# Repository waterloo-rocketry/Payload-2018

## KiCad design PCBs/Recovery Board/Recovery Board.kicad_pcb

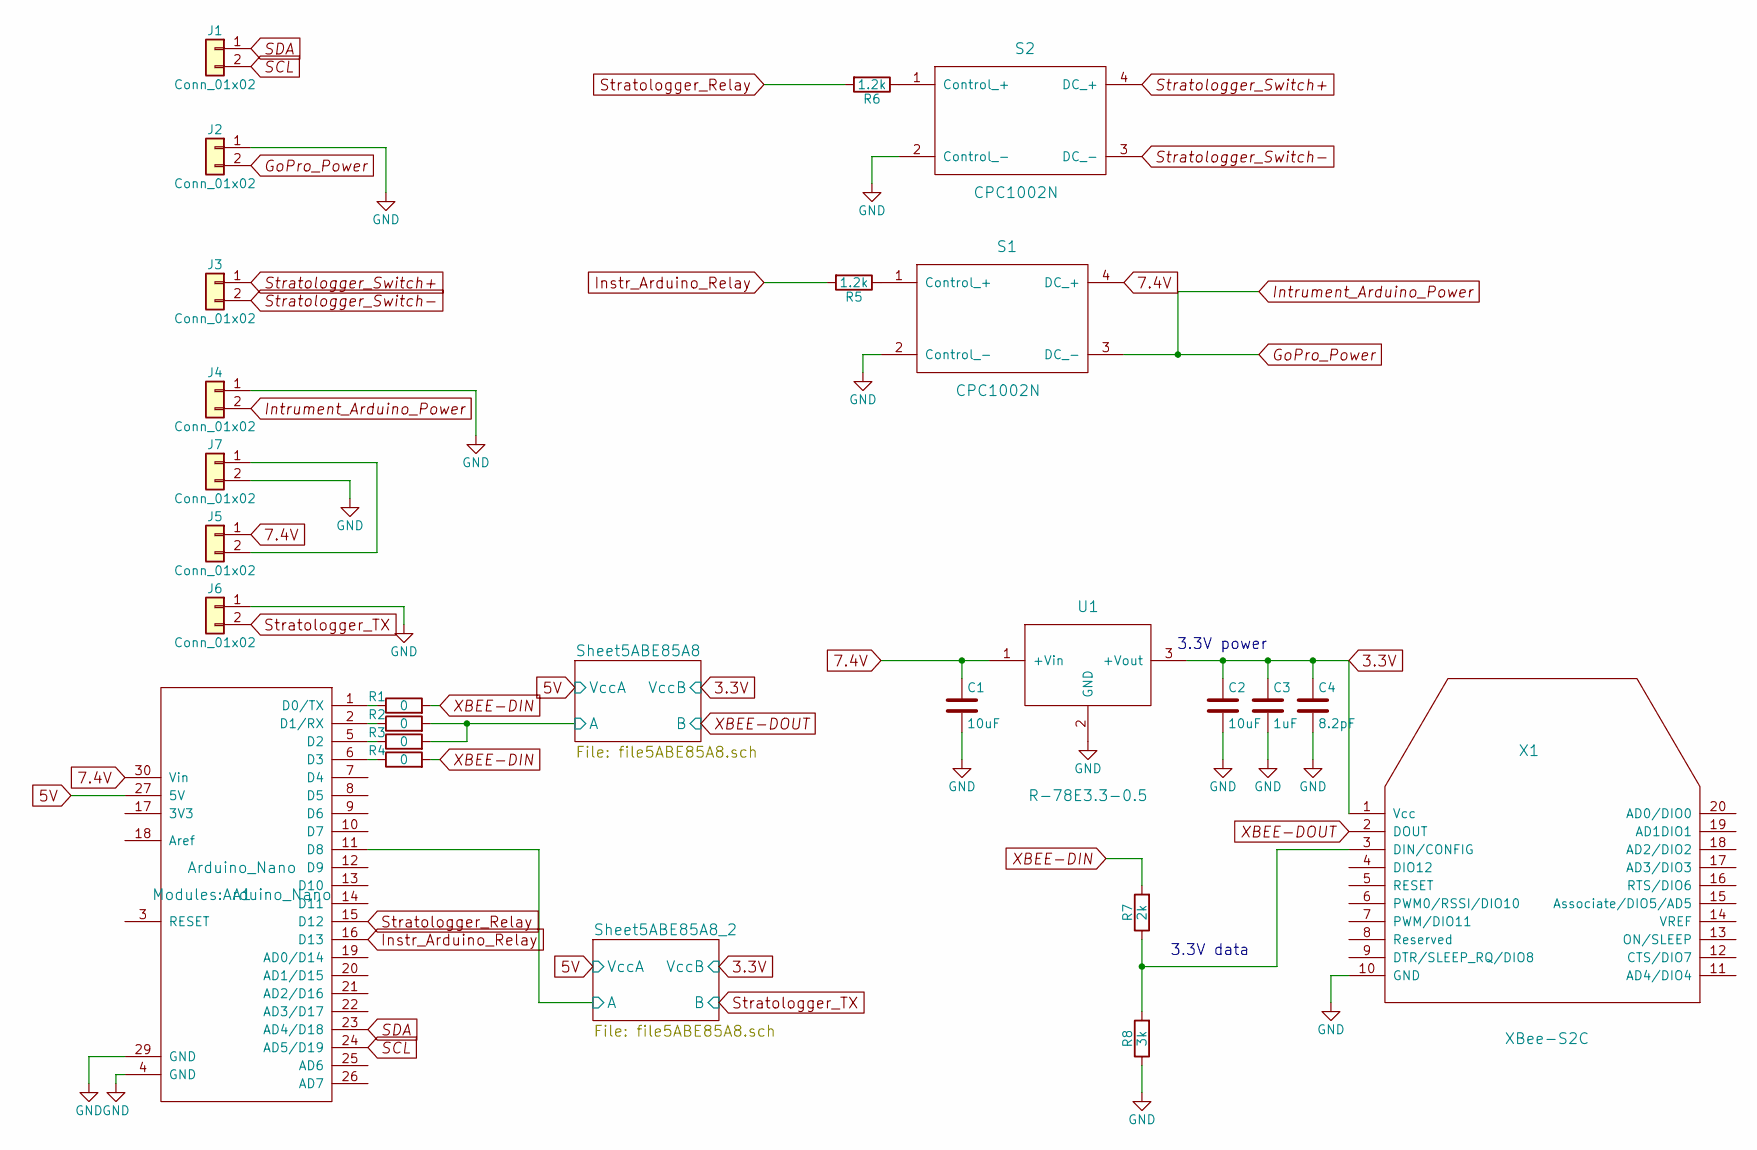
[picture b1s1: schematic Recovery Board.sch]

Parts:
A1: Arduino_Nano
C1, C2: 10uF; C_0805_HandSoldering
C3: 1uF; C_0805_HandSoldering
C4: 8.2pF; C_0805_HandSoldering
J1, J2, J3, J4, J6: Conn_01x02; molex_kk_22-23-2021
J5, J7: Conn_01x02; JST_PH_B2B-PH-K_02x2.00mm_Straight
R1, R2, R3, R4: 0; R_0805_HandSoldering
R5, R6: 1.2k; R_0805_HandSoldering
R7: 2k; R_0805_HandSoldering
R8: 3k; R_0805_HandSoldering
S1, S2: CPC1002N; CPC1002NTR
U1: R-78E3.3-0.5; SIP3
X1: XBee-S2C; XBEE-1

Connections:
3.3V: C2.1, C3.1, C4.1, U1.3 (+Vout), X1.1 (Vcc); also elsewhere on the board
5V: A1.27 (5V); also elsewhere on the board
7.4V: A1.30 (Vin), C1.1, J5.1, S1.4 (DC_+), U1.1 (+Vin)
/Sheet5ABE85A8/A: R2.2, R3.2; also elsewhere on the board
/Sheet5ABE85A8_2/A: A1.11 (D8); also elsewhere on the board
GND: A1.4 (GND), A1.29 (GND), C1.2, C2.2, C3.2, C4.2, J2.1, J4.1, J6.1, J7.2, R8.1, S1.2 (Control_-), S2.2 (Control_-), U1.2 (GND), X1.10 (GND); also elsewhere on the board
GoPro_Power: J2.2, J4.2, S1.3 (DC_-)
Instr_Arduino_Relay: A1.16 (D13), R5.2
unnamed: A1.1 (D0/TX), R1.1
unnamed: A1.2 (D1/RX), R2.1
unnamed: A1.5 (D2), R3.1
unnamed: A1.6 (D3), R4.1
unnamed: J5.2, J7.1
unnamed: R5.1, S1.1 (Control_+)
unnamed: R6.1, S2.1 (Control_+)
unnamed: R7.1, R8.2, X1.3 (DIN/CONFIG)
SCL: A1.24 (AD5/D19), J1.2
SDA: A1.23 (AD4/D18), J1.1
Stratologger_Relay: A1.15 (D12), R6.2
Stratologger_Switch+: J3.1, S2.4 (DC_+)
Stratologger_Switch-: J3.2, S2.3 (DC_-)
Stratologger_TX: J6.2; also elsewhere on the board
XBEE-DIN: R1.2, R4.2, R7.2
XBEE-DOUT: X1.2 (DOUT); also elsewhere on the board

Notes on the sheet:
3.3V data
3.3V power

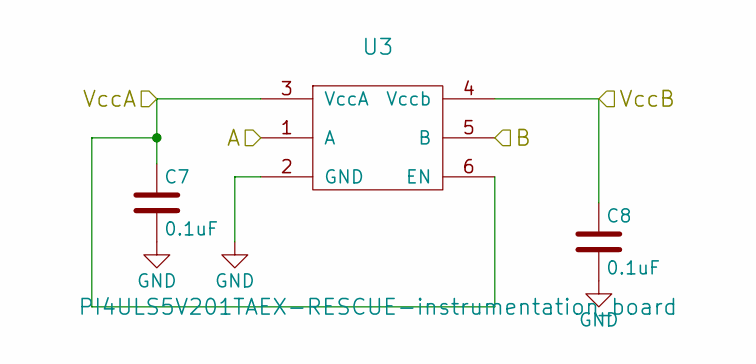
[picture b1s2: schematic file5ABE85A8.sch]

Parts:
C5, C6: 0.1uF; C_0805_HandSoldering
U2: PI4ULS5V201TAEX-RESCUE-instrumentation_board; SOT-23-6_Handsoldering

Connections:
3.3V: C6.1, U2.4 (Vccb); also elsewhere on the board
5V: C5.1, U2.3 (VccA), U2.6 (EN); also elsewhere on the board
/Sheet5ABE85A8/A: U2.1 (A); also elsewhere on the board
GND: C5.2, C6.2, U2.2 (GND); also elsewhere on the board
XBEE-DOUT: U2.5 (B); also elsewhere on the board

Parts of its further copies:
C7, C8: 0.1uF; C_0805_HandSoldering
U3: PI4ULS5V201TAEX-RESCUE-instrumentation_board; SOT-23-6_Handsoldering

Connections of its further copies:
3.3V: C8.1, U3.4 (Vccb); also elsewhere on the board
5V: C7.1, U3.3 (VccA), U3.6 (EN); also elsewhere on the board
/Sheet5ABE85A8_2/A: U3.1 (A); also elsewhere on the board
GND: C7.2, C8.2, U3.2 (GND); also elsewhere on the board
Stratologger_TX: U3.5 (B); also elsewhere on the board

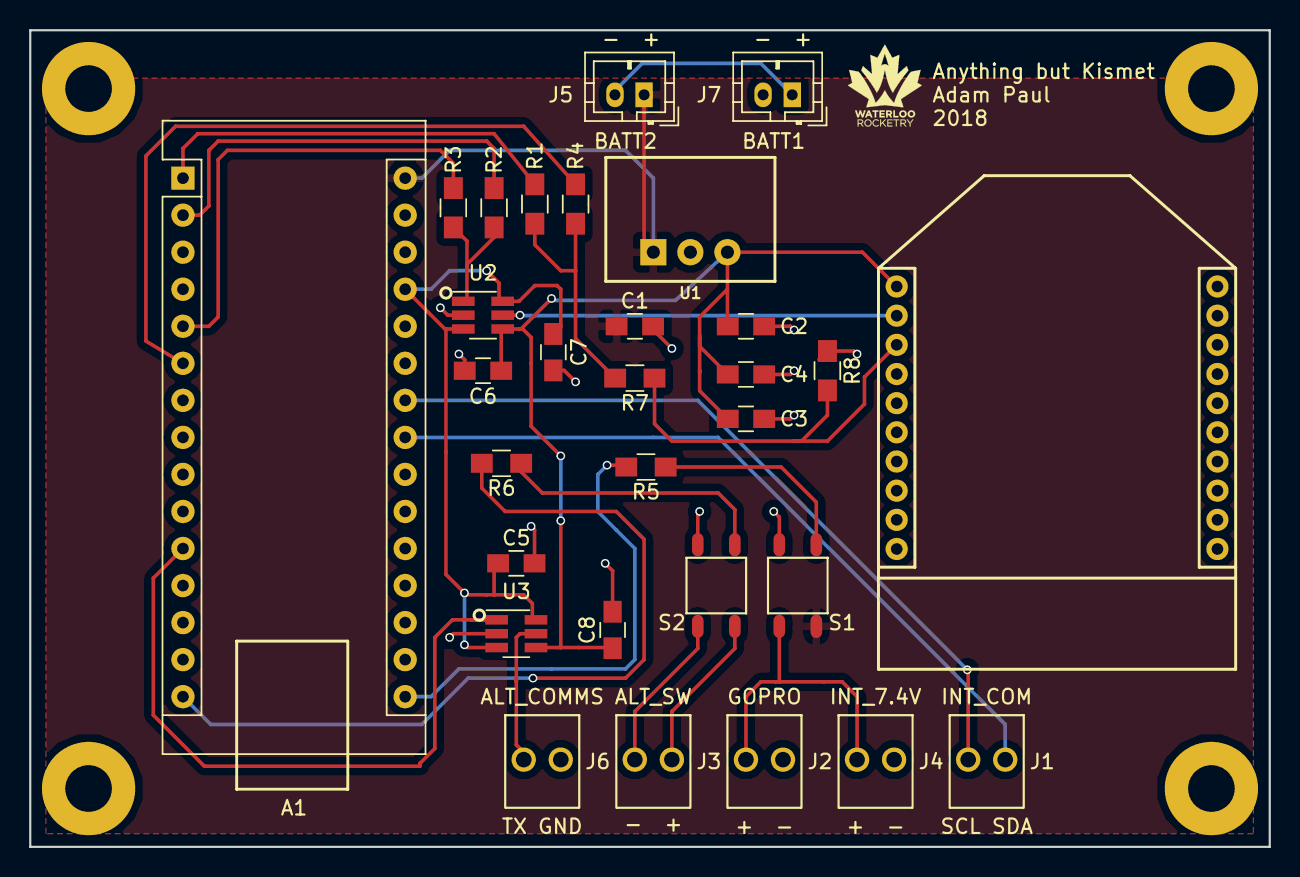
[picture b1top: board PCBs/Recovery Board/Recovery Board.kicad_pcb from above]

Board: 2 copper layers, 85.0 x 56.0 mm, 30 parts (0 on the bottom side), 24 nets.

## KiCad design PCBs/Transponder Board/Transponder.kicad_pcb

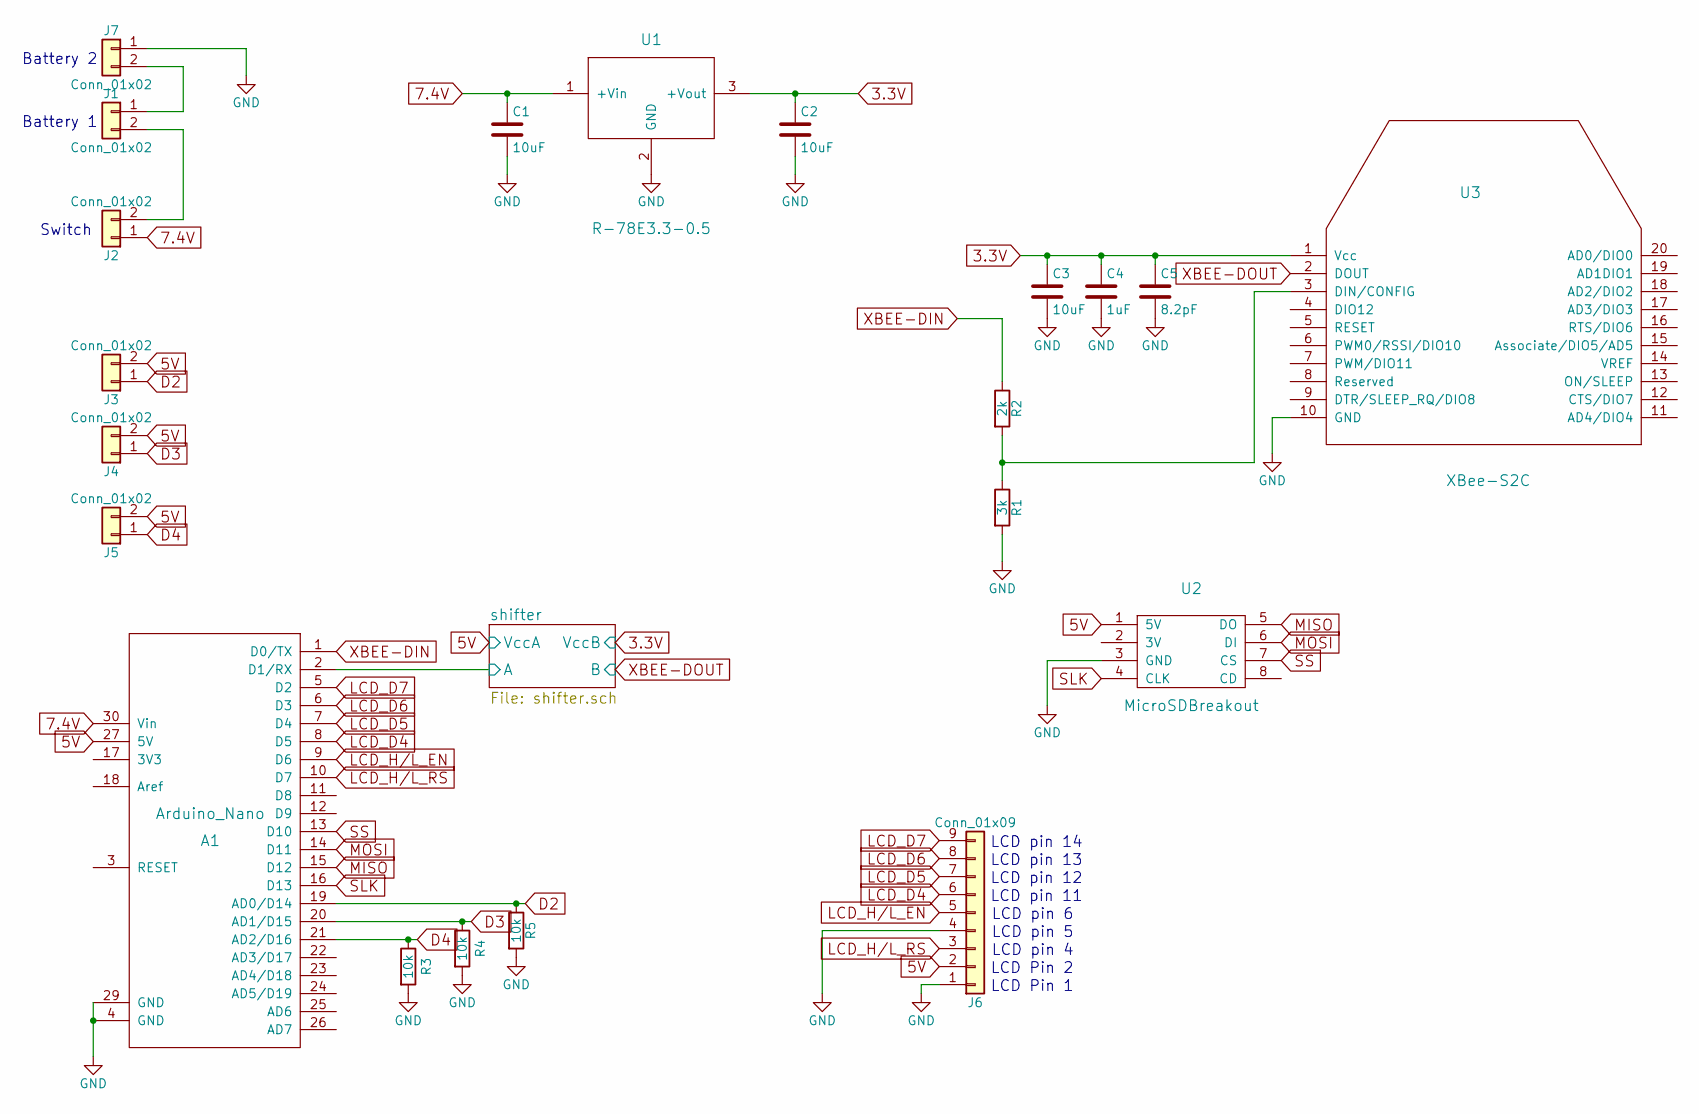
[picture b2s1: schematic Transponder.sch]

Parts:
A1: Arduino_Nano
C1, C2, C3: 10uF; C_0805_HandSoldering
C4: 1uF; C_0805_HandSoldering
C5: 8.2pF; C_0805_HandSoldering
J1, J7: Conn_01x02; JST_PH_B2B-PH-K_02x2.00mm_Straight
J2, J3, J4, J5: Conn_01x02; molex_kk_22-23-2021
J6: Conn_01x09; VI0921550000G
R1: 3k; R_0805_HandSoldering
R2: 2k; R_0805_HandSoldering
R3, R4, R5: 10k; R_0805_HandSoldering
U1: R-78E3.3-0.5; SIP3Large
U2: MicroSDBreakout; adafruit254
U3: XBee-S2C; XBEE-1

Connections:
3.3V: C2.1, C3.1, C4.1, C5.1, U1.3 (+Vout), U3.1 (Vcc); also elsewhere on the board
5V: A1.27 (5V), J3.2, J4.2, J5.2, J6.2, U2.1 (5V); also elsewhere on the board
7.4V: A1.30 (Vin), C1.1, J2.1, U1.1 (+Vin)
/shifter/A: A1.2 (D1/RX); also elsewhere on the board
D2: A1.19 (AD0/D14), J3.1, R5.1
D3: A1.20 (AD1/D15), J4.1, R4.1
D4: A1.21 (AD2/D16), J5.1, R3.1
GND: A1.4 (GND), A1.29 (GND), C1.2, C2.2, C3.2, C4.2, C5.2, J6.1, J6.4, J7.1, R1.2, R3.2, R4.2, R5.2, U1.2 (GND), U2.3 (GND), U3.10 (GND); also elsewhere on the board
LCD_D4: A1.8 (D5), J6.6
LCD_D5: A1.7 (D4), J6.7
LCD_D6: A1.6 (D3), J6.8
LCD_D7: A1.5 (D2), J6.9
LCD_H/L_EN: A1.9 (D6), J6.5
LCD_H/L_RS: A1.10 (D7), J6.3
MISO: A1.15 (D12), U2.5 (DO)
MOSI: A1.14 (D11), U2.6 (DI)
unnamed: J1.1, J7.2
unnamed: J1.2, J2.2
unnamed: R1.1, R2.2, U3.3 (DIN/CONFIG)
SLK: A1.16 (D13), U2.4 (CLK)
SS: A1.13 (D10), U2.7 (CS)
XBEE-DIN: A1.1 (D0/TX), R2.1
XBEE-DOUT: U3.2 (DOUT); also elsewhere on the board

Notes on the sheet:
LCD Pin 1
LCD Pin 2
LCD pin 4
LCD pin 5
LCD pin 6
LCD pin 11
LCD pin 12
LCD pin 13
LCD pin 14
Battery 1
Switch
Battery 2

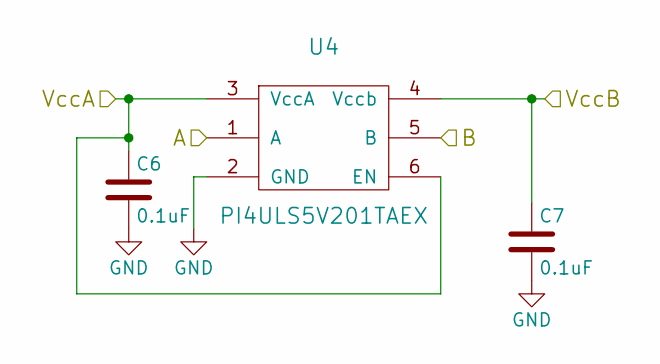
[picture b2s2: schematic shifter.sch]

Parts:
C6, C7: 0.1uF; C_0805_HandSoldering
U4: PI4ULS5V201TAEX; SOT-23-6_Handsoldering

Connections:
3.3V: C7.1, U4.4 (Vccb); also elsewhere on the board
5V: C6.1, U4.3 (VccA), U4.6 (EN); also elsewhere on the board
/shifter/A: U4.1 (A); also elsewhere on the board
GND: C6.2, C7.2, U4.2 (GND); also elsewhere on the board
XBEE-DOUT: U4.5 (B); also elsewhere on the board

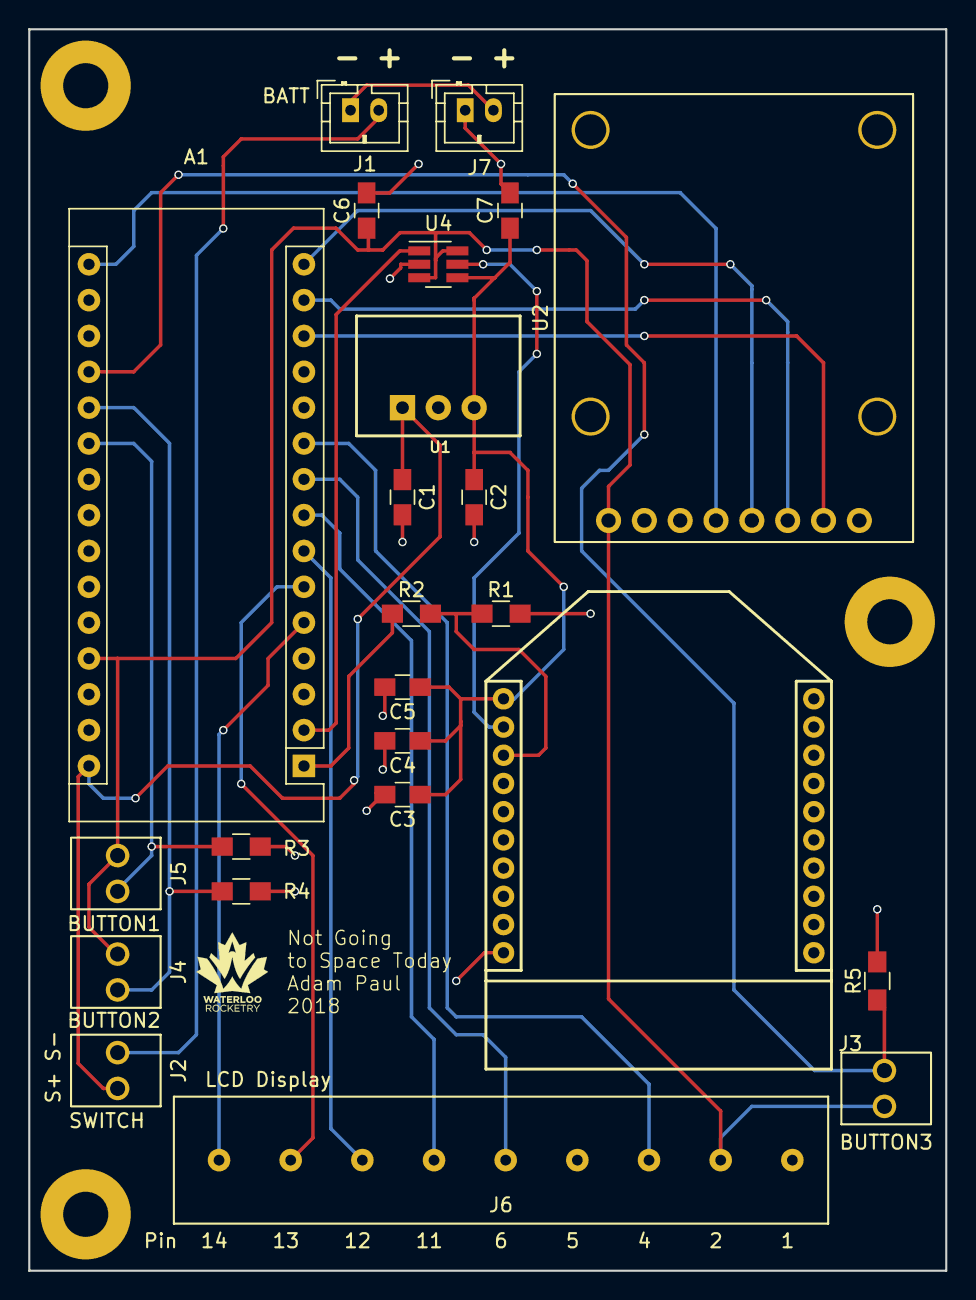
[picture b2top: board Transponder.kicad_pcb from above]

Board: 2 copper layers, 65.0 x 88.0 mm, 24 parts (0 on the bottom side), 23 nets.

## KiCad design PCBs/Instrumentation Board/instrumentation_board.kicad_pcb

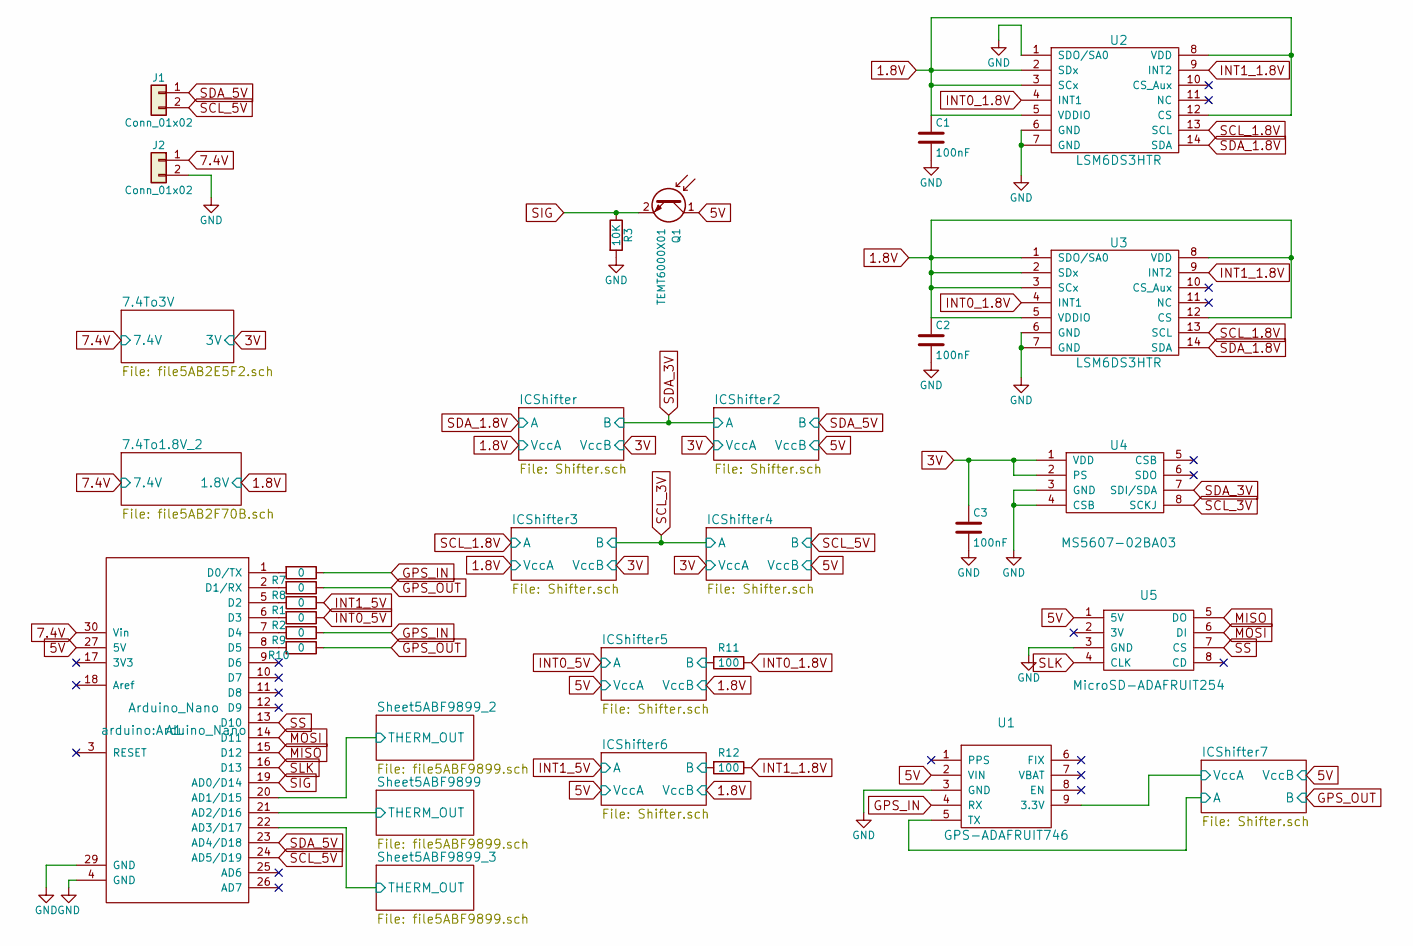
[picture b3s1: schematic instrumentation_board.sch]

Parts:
A1: Arduino_Nano
C1, C2, C3: 100nF; C_0805_HandSoldering
J1, J2: Conn_01x02; molex_kk_22-23-2021
Q1: TEMT6000X01
R1, R2, R7, R8, R9, R10: 0; R_0805_HandSoldering
R3: 10K; R_0805_HandSoldering
R11, R12: 100; R_0805_HandSoldering
U1: GPS-ADAFRUIT746; gps746
U2, U3: LSM6DS3HTR; LGA-14
U4: MS5607-02BA03; 8-SMD
U5: MicroSD-ADAFRUIT254; adafruit254

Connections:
1.8V: C1.1, C2.1, U2.2 (SDx), U2.3 (SCx), U2.5 (VDDIO), U2.8 (VDD), U2.12 (CS), U3.1 (SDO/SA0), U3.2 (SDx), U3.3 (SCx), U3.5 (VDDIO), U3.8 (VDD), U3.12 (CS); also elsewhere on the board
3V: C3.1, U4.1 (VDD), U4.2 (PS); also elsewhere on the board
5V: A1.27 (5V), Q1.1 (C), U1.2 (VIN), U5.1 (5V); also elsewhere on the board
7.4V: A1.30 (Vin), J2.1; also elsewhere on the board
/ICShifter7/A: U1.5 (TX); also elsewhere on the board
/ICShifter7/VccA: U1.9 (3.3V); also elsewhere on the board
/Sheet5ABF9899/THERM_OUT: A1.21 (AD2/D16); also elsewhere on the board
/Sheet5ABF9899_2/THERM_OUT: A1.20 (AD1/D15); also elsewhere on the board
/Sheet5ABF9899_3/THERM_OUT: A1.22 (AD3/D17); also elsewhere on the board
GND: A1.4 (GND), A1.29 (GND), C1.2, C2.2, C3.2, J2.2, R3.2, U1.3 (GND), U2.1 (SDO/SA0), U2.6 (GND), U2.7 (GND), U3.6 (GND), U3.7 (GND), U4.3 (GND), U4.4 (CSB), U5.3 (GND); also elsewhere on the board
GPS_IN: R7.1, R9.1, U1.4 (RX)
GPS_OUT: R8.1, R10.1; also elsewhere on the board
INT0_5V: R2.1; also elsewhere on the board
INT1_5V: R1.1; also elsewhere on the board
MISO: A1.15 (D12), U5.5 (DO)
MOSI: A1.14 (D11), U5.6 (DI)
unnamed: A1.1 (D0/TX), R7.2
unnamed: A1.2 (D1/RX), R8.2
unnamed: A1.5 (D2), R1.2
unnamed: A1.6 (D3), R2.2
unnamed: A1.7 (D4), R9.2
unnamed: A1.8 (D5), R10.2
SCL_1.8V: U2.13 (SCL), U3.13 (SCL); also elsewhere on the board
SCL_3V: U4.8 (SCKJ); also elsewhere on the board
SCL_5V: A1.24 (AD5/D19), J1.2; also elsewhere on the board
SDA_1.8V: U2.14 (SDA), U3.14 (SDA); also elsewhere on the board
SDA_3V: U4.7 (SDI/SDA); also elsewhere on the board
SDA_5V: A1.23 (AD4/D18), J1.1; also elsewhere on the board
SIG: A1.19 (AD0/D14), Q1.2 (E), R3.1
SLK: A1.16 (D13), U5.4 (CLK)
SS: A1.13 (D10), U5.7 (CS)

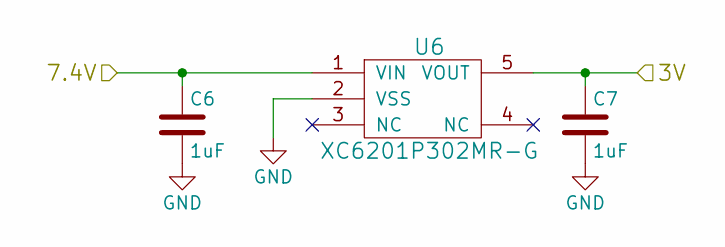
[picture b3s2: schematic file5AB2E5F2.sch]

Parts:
C6, C7: 1uF
U6: XC6201P302MR-G; SOT-23-5

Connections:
3V: C7.1, U6.5 (VOUT); also elsewhere on the board
7.4V: C6.1, U6.1 (VIN); also elsewhere on the board
GND: C6.2, C7.2, U6.2 (VSS); also elsewhere on the board

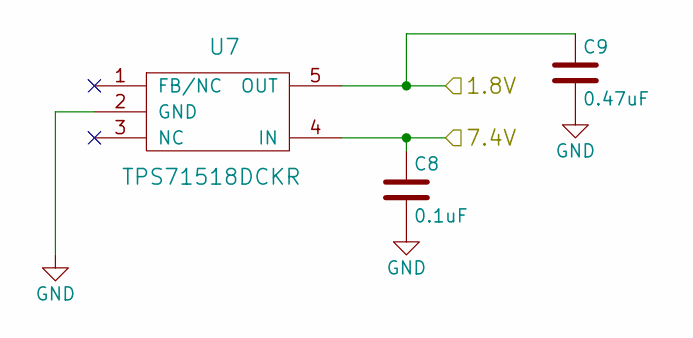
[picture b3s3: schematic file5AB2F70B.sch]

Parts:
C8: 0.1uF; C_0805_HandSoldering
C9: 0.47uF; C_0805_HandSoldering
U7: TPS71518DCKR; SOT-23-5

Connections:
1.8V: C9.1, U7.5 (OUT); also elsewhere on the board
7.4V: C8.1, U7.4 (IN); also elsewhere on the board
GND: C8.2, C9.2, U7.2 (GND); also elsewhere on the board

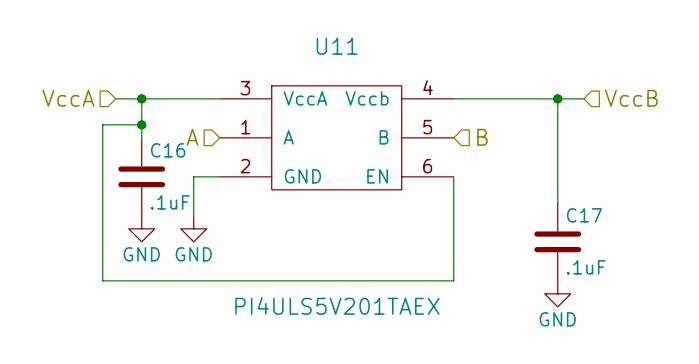
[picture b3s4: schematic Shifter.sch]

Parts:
C10, C11: .1uF; C_0805_HandSoldering
U8: PI4ULS5V201TAEX; SOT-23-6_Handsoldering

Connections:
3V: C10.1, U8.3 (VccA), U8.6 (EN); also elsewhere on the board
5V: C11.1, U8.4 (Vccb); also elsewhere on the board
GND: C10.2, C11.2, U8.2 (GND); also elsewhere on the board
SCL_3V: U8.1 (A); also elsewhere on the board
SCL_5V: U8.5 (B); also elsewhere on the board

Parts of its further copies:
C12, C13, C14, C15, C16, C17, C18, C19, C20, C21, C22, C23: .1uF; C_0805_HandSoldering
U9, U10, U11, U12, U13, U14: PI4ULS5V201TAEX; SOT-23-6_Handsoldering

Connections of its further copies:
1.8V: C12.1, C16.1, C21.1, C23.1, U9.3 (VccA), U9.6 (EN), U11.3 (VccA), U11.6 (EN), U13.4 (Vccb), U14.4 (Vccb); also elsewhere on the board
3V: C13.1, C14.1, C17.1, U9.4 (Vccb), U10.3 (VccA), U10.6 (EN), U11.4 (Vccb); also elsewhere on the board
5V: C15.1, C19.1, C20.1, C22.1, U10.4 (Vccb), U12.4 (Vccb), U13.3 (VccA), U13.6 (EN), U14.3 (VccA), U14.6 (EN); also elsewhere on the board
/ICShifter7/A: U12.1 (A); also elsewhere on the board
/ICShifter7/VccA: C18.1, U12.3 (VccA), U12.6 (EN); also elsewhere on the board
GND: C12.2, C13.2, C14.2, C15.2, C16.2, C17.2, C18.2, C19.2, C20.2, C21.2, C22.2, C23.2, U9.2 (GND), U10.2 (GND), U11.2 (GND), U12.2 (GND), U13.2 (GND), U14.2 (GND); also elsewhere on the board
GPS_OUT: U12.5 (B); also elsewhere on the board
INT0_5V: U13.1 (A); also elsewhere on the board
INT1_5V: U14.1 (A); also elsewhere on the board
SCL_1.8V: U9.1 (A); also elsewhere on the board
SCL_3V: U9.5 (B); also elsewhere on the board
SDA_1.8V: U11.1 (A); also elsewhere on the board
SDA_3V: U10.1 (A), U11.5 (B); also elsewhere on the board
SDA_5V: U10.5 (B); also elsewhere on the board

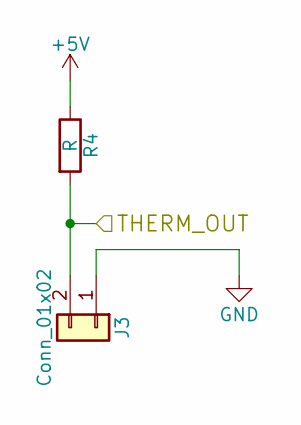
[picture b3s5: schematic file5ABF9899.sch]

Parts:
J3: Conn_01x02; molex_kk_22-23-2021
R4: R

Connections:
5V: R4.1; also elsewhere on the board
/Sheet5ABF9899_2/THERM_OUT: J3.2, R4.2; also elsewhere on the board
GND: J3.1; also elsewhere on the board

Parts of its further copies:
J4, J5: Conn_01x02; molex_kk_22-23-2021
R5, R6: R

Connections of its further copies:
5V: R5.1, R6.1; also elsewhere on the board
/Sheet5ABF9899/THERM_OUT: J4.2, R5.2; also elsewhere on the board
/Sheet5ABF9899_3/THERM_OUT: J5.2, R6.2; also elsewhere on the board
GND: J4.1, J5.1; also elsewhere on the board

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
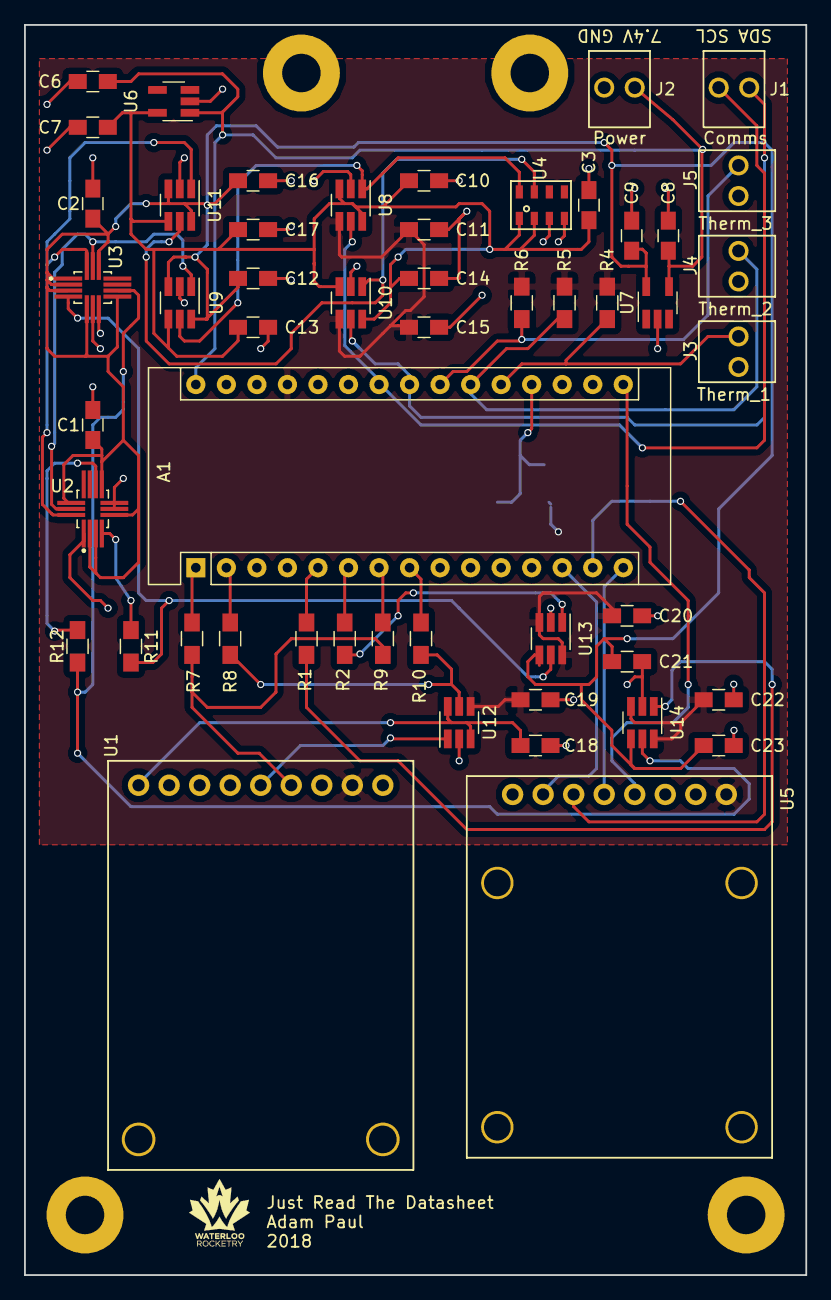
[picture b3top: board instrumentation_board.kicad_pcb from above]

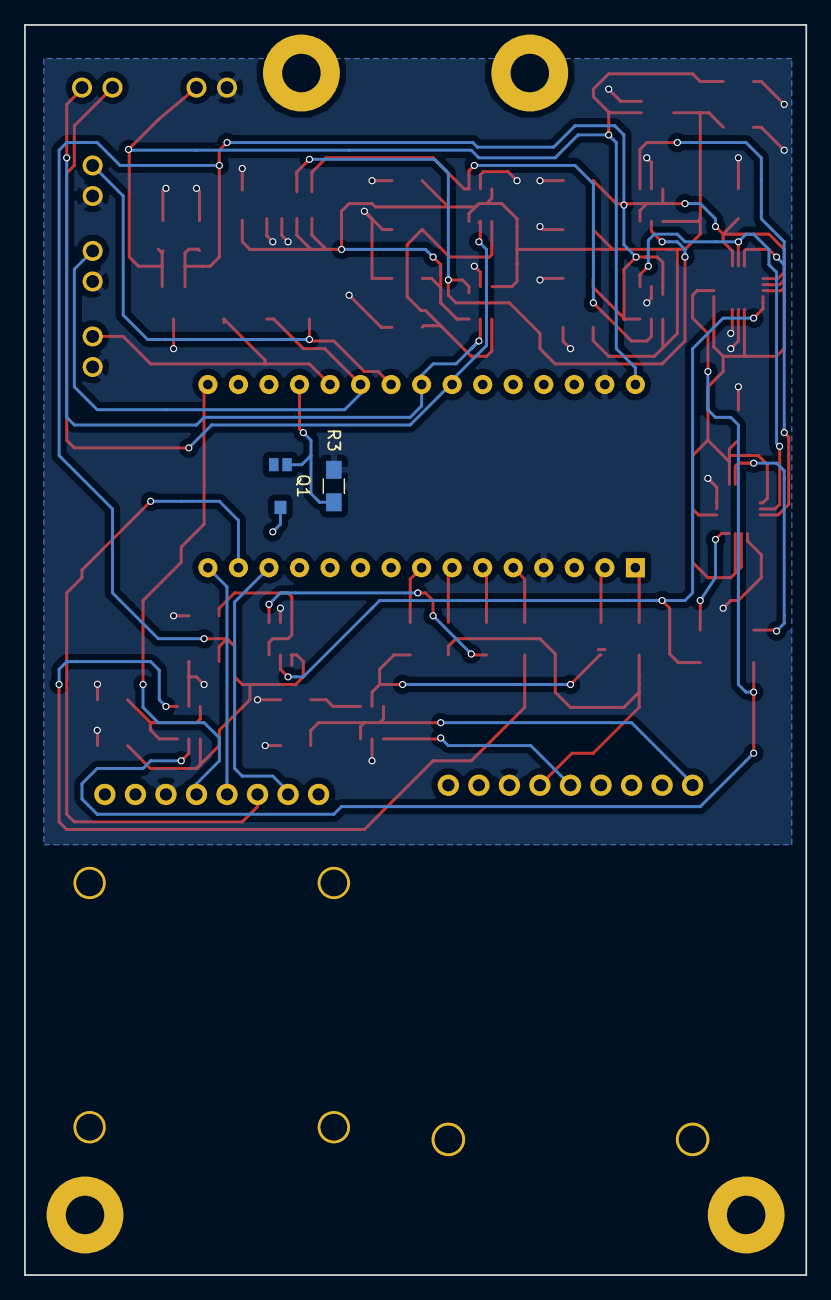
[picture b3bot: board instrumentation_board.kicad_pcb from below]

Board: 2 copper layers, 65.0 x 104.0 mm, 54 parts (2 on the bottom side), 35 nets.

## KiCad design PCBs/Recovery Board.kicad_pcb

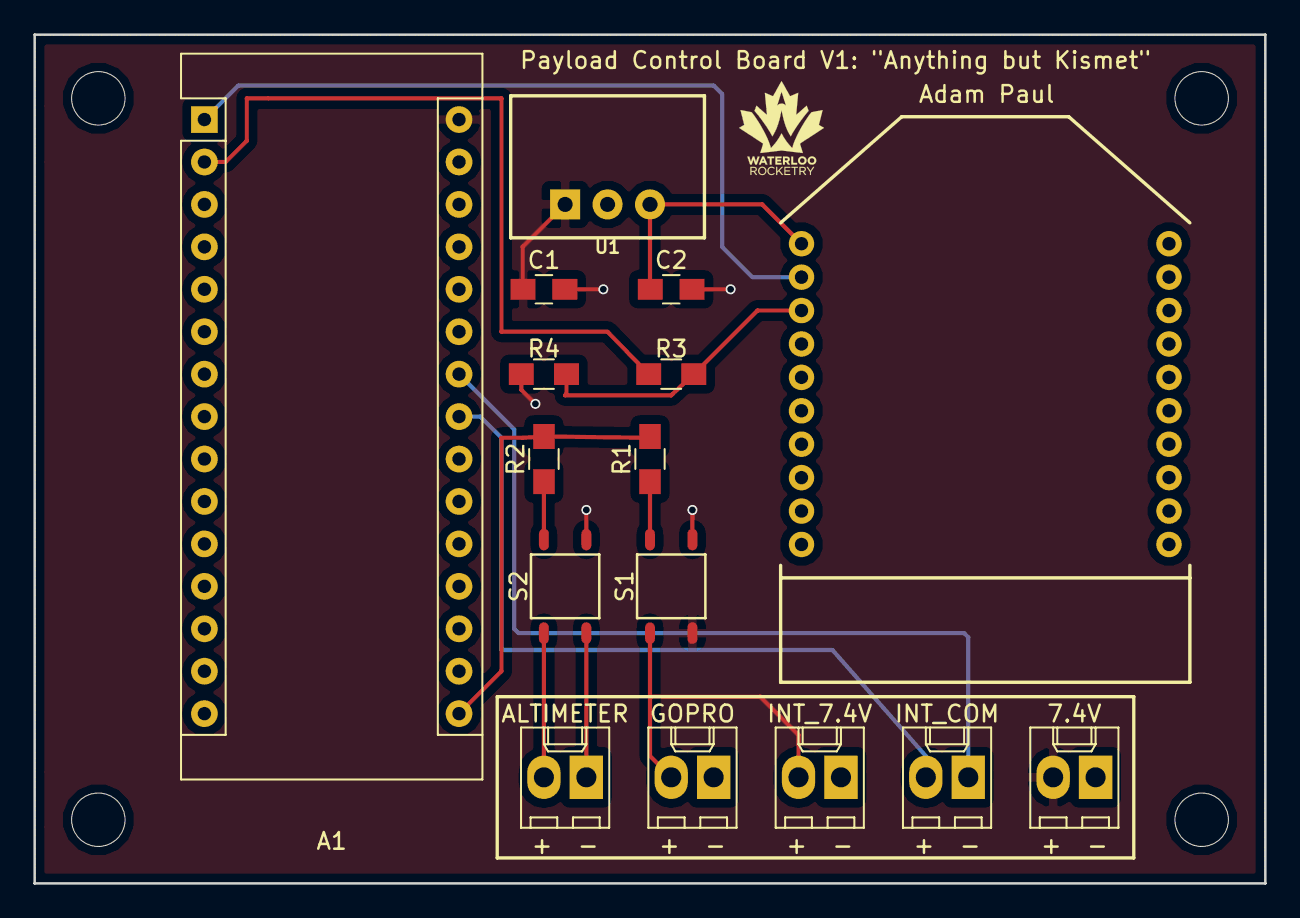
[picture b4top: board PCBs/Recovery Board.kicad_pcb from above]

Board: 2 copper layers, 73.7 x 50.8 mm, 16 parts (0 on the bottom side), 14 nets.

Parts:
7.4V: Conn_01x02; Molex_KK-6410-02_02x2.54mm_Straight
A1: Arduino_Nano
ALTIMETER: Conn_01x02; Molex_KK-6410-02_02x2.54mm_Straight
C1, C2: 10uF; C_0805_HandSoldering
GOPRO: Conn_01x02; Molex_KK-6410-02_02x2.54mm_Straight
INT_7.4V: Conn_01x02; Molex_KK-6410-02_02x2.54mm_Straight
INT_COM: Conn_01x02; Molex_KK-6410-02_02x2.54mm_Straight
R1, R2: 1.9k; R_0805_HandSoldering
R3: R3; R_0805_HandSoldering
R4: R4; R_0805_HandSoldering
S1, S2: CPC1002N; CPC1002NTR
U1: R-78E3.3-0.5; SIP3
X1: XBee-S2C; XBEE-1

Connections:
7.4V: 7.4V.2, A1.30, C1.1, S1.4, U1.1
GND: 7.4V.1, A1.4, A1.29, C1.2, C2.2, GOPRO.1, INT_7.4V.1, R4.1, S1.2, S2.2, U1.2, X1.10
GoPro_Power: GOPRO.2, INT_7.4V.2, S1.3
INSTRUMENT_ARDUINO_COMMS1: A1.23, INT_COM.2
INSTRUMENT_ARDUINO_COMMS2: A1.24, INT_COM.1
unnamed: R3.1, R4.2, X1.3
unnamed: A1.16, R1.2, R2.2
unnamed: C2.1, U1.3, X1.1
unnamed: R1.1, S1.1
unnamed: R2.1, S2.1
Stratologger_Switch+: ALTIMETER.2, S2.3
Stratologger_Switch-: ALTIMETER.1, S2.4
XBEE-DIN: A1.2, R3.2
XBEE-DOUT: A1.1, X1.2

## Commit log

2018-03-06 Fixed grounds and missing terminal
2018-03-08 Instrumentation board
2018-03-13 Instrumentation board for review
2018-03-14 Changes requested by alex
2018-03-21 added some new parts and i2c bus changes
2018-03-24 replace bidirectional shifters with ICs
2018-03-24 fixed swapped pins
2018-03-25 transponder board
2018-03-26 changes as per Alex's review
2018-03-27 pinout changes
2018-03-28 stashing changes
2018-03-28 Re-annotated
2018-03-28 Netlist Genorated
    Fixed multiple sheets with same name issue, generated netlist
2018-03-28 Started instrumentation Netlist
    Finished footprints for shifter, regulators and IMUs
2018-03-29 Continuing netlist
    Added barometric pressure sensor, started pattern for SD breakout board
2018-03-30 added various review changes
2018-03-30 swapped TX and RX pins
2018-03-30 weird merge
2018-03-30 Footprints updated
2018-03-31 Fixed weird merge issue (2)
2018-03-31 Added BOM and software outline
2018-03-31 testing slack integration
2018-04-01 review changes + instr board PCB
2018-04-01 finished traces on instr board
2018-04-01 edge cuts and screw holes
2018-04-03 Updated Recovery Netlist, started board updated layout
2018-04-03 completed layout for transponder board
2018-04-04 Continued new recovery board layout
2018-04-04 rerouted payload instr board and completed all changes per Alexs review
2018-04-04 transponder changes as per Alexs review
2018-04-04 fixed some outstanding instr issues, removed lots of vias
2018-04-04 Finished updating recovery board layout
    board layout, schematic and netlist up to date
2018-04-05 fixed outstanding changes on instr and transponder board
2018-04-06 swapped all mounting holes with plated ones, fixed disconnected components on recovery, added the 4 decoupling caps to recovery, fixed silk screen on pads in instr, fixed traces connecting through pa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
2018-04-07 Changed connectors for recovery board batteries
    Added a second connector for the other battery
    Moved connectors to top of board
    Replaced footprint with JST-PH
    Extended board width
2018-04-08 Changes to instr connectors
    Extended instr board length
    moved power connector to top of board
    removed I2C connector to top of board
2018-04-08 Fixed instr and recovery components per Alexs review
    Added IMU current limiting resistors
    Moved the caps near J4 on instr
    Swapped out phototransistor footprint
    Flipped I2C silk screen on J1 recovery
    Flipped GND and TX silk screen on J6 recovery
    renamed strat to alt on recovery silk screen
2018-04-09 Current limiting resistors
    Fixed structure of current limiting resistors on instr arduino
2018-04-09 Added Gerber Files
2018-04-10 Re-exported gerber
2018-04-10 Connector Changes
    Flipped the transponder jst-ph connectors
    Replaced the molex footprint on recovery with the correct one
2018-04-11 Re-Exported Gerber files with .05mm solder mask clearance
2018-04-11 Added zips for gerber files
2018-04-12 Started RecoverBoard Code
    Most code has been implemented except for softwareserial
2018-04-12 Updated BOM
2018-04-13 more BOM updating
2018-04-15 Final BOM
2018-04-16 Changes to PseudoCode
    Added a timer to turn off recovery after 1 hour
    Finished core update loop for instr
    Wrote all of transponder
2018-04-18 added a first draft of payload communications guidelines
2018-04-20 restucture of recovery code for new comm standard
2018-04-20 More recovery board code
2018-04-24 started transponder code
2018-04-25 added logic for receiving messages on transponder
2018-04-29 updated working transponder build
2018-05-01 finished core transponder and recovery loop
2018-05-01 Started framework for instr board
2018-05-02 communication between instr board and transponder
2018-05-02 code refactor
2018-05-05 Added support for IMU and pressure sensors
2018-05-05 Added support for SD logging on cubesat side
2018-05-06 Added SD support for transponder board
2018-05-07 Changes to recovery board to fix found issues
    Swapped pin 1 & 2 on the CPC1002N relays
    Removed the screen from the back of the xbee pins
    Added an indicator for the install direction for arduino
2018-05-07 Changes to instr board from errors found
    Added a direction indicator to arduino
    Swapped the GPS pin order
2018-05-10 New recovery gerbers
2018-05-10 Added recovery zip
2018-05-10 Fixed top level pour for recovery
2018-05-19 Switched over GPS library to avoid I2C conflicts
2018-05-24 added SD and 2nd IMU support to instr
2018-05-25 Beginning of transponder UI refactor
2018-05-31 Fixed SD logic on instr side, added detection for a bad SD card on transponder side
2018-06-01 fixes for SD card transponder issues, added thermistors
2018-06-02 added support for altimeter status verification
2018-06-02 Added Testing Plan
2018-06-04 added packing list
2018-06-16 pre-comp code lockdown
